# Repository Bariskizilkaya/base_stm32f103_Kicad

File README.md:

# base_stm32f103_Kicad
Kicad based stm32f103 base desing

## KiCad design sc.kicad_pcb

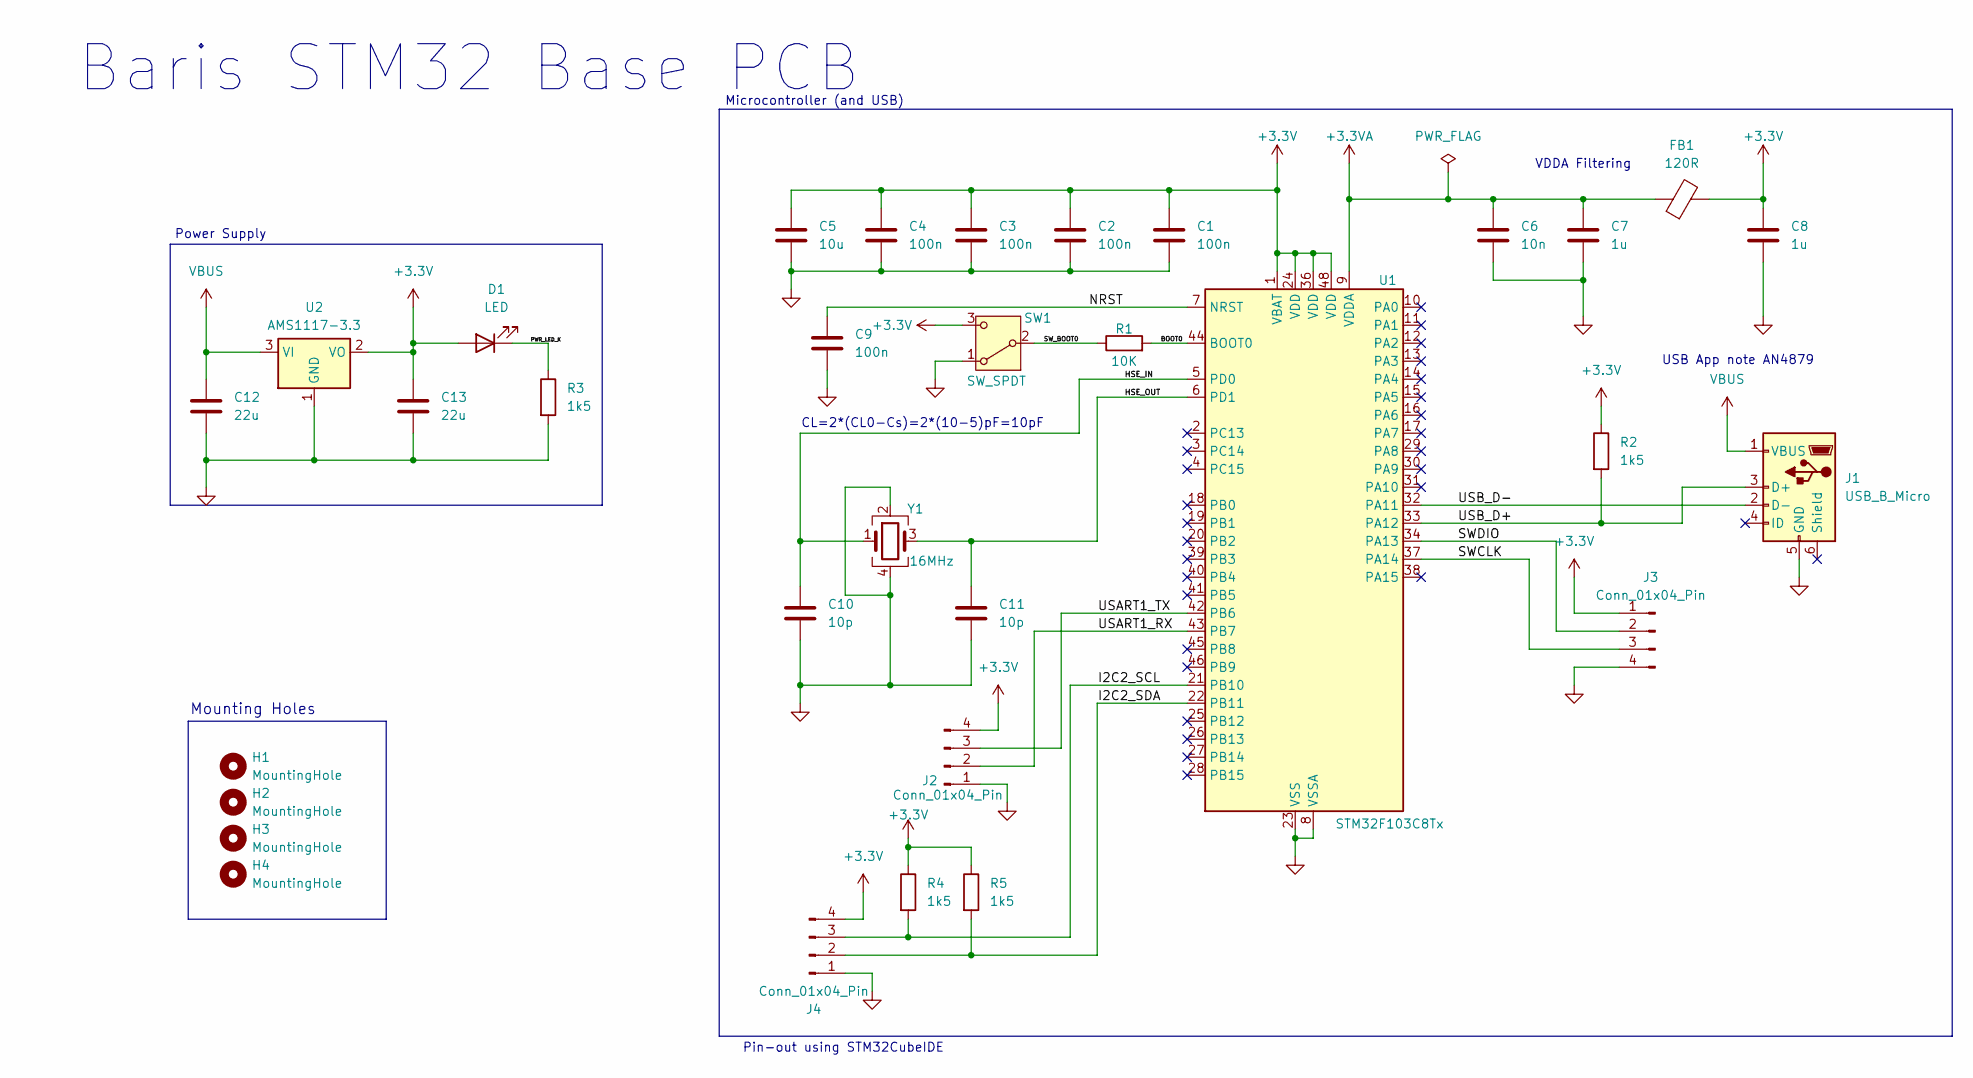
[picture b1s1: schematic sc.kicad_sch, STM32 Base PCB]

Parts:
C1, C2, C3, C4, C9: 100n; C_0402_1005Metric
C5: 10u; C_0603_1608Metric
C6: 10n; C_0402_1005Metric
C7, C8: 1u; C_0402_1005Metric
C10, C11: 10p; C_0402_1005Metric
C12, C13: 22u; C_0805_2012Metric
D1: LED; LED_0603_1608Metric
FB1: 120R; L_0603_1608Metric
H1, H2, H3, H4: MountingHole; MountingHole_2.2mm_M2
J1: USB_B_Micro; USB_Micro-B_Wuerth_629105150521
J2, J3, J4: Conn_01x04_Pin; PinHeader_1x04_P2.54mm_Vertical
R1: 10K; R_0402_1005Metric
R2, R3, R4, R5: 1k5; R_0402_1005Metric
SW1: SW_SPDT; SW_SPDT_PCM12
U1: STM32F103C8Tx; LQFP-48_7x7mm_P0.5mm
U2: AMS1117-3.3; SOT-223-3_TabPin2
Y1: 16MHz; Crystal_SMD_3225-4Pin_3.2x2.5mm

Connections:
+3.3V: C1.1, C2.1, C3.1, C4.1, C5.1, C8.1, C13.1, D1.2 (A), FB1.2, J2.4, J3.1, J4.4, R2.1, R4.1, R5.1, SW1.3 (C), U1.1 (VBAT), U1.24 (VDD), U1.36 (VDD), U1.48 (VDD), U2.2 (VO)
+3.3VA: C6.1, C7.1, FB1.1, U1.9 (VDDA)
/BOOT0: R1.2, U1.44 (BOOT0)
/HSE_IN: C10.1, U1.5 (PD0), Y1.1
/HSE_OUT: C11.1, U1.6 (PD1), Y1.3
/I2C2_SCL: J4.3, R4.2, U1.21 (PB10)
/I2C2_SDA: J4.2, R5.2, U1.22 (PB11)
/NRST: C9.1, U1.7 (NRST)
/PWR_LED_K: D1.1 (K), R3.1
/SWCLK: J3.3, U1.37 (PA14)
/SWDIO: J3.2, U1.34 (PA13)
/SW_BOOT0: R1.1, SW1.2 (B)
/USART1_RX: J2.2, U1.43 (PB7)
/USART1_TX: J2.3, U1.42 (PB6)
/USB_D+: J1.3 (D+), R2.2, U1.33 (PA12)
/USB_D-: J1.2 (D-), U1.32 (PA11)
GND: C1.2, C2.2, C3.2, C4.2, C5.2, C6.2, C7.2, C8.2, C9.2, C10.2, C11.2, C12.2, C13.2, J1.5 (GND), J2.1, J3.4, J4.1, R3.2, SW1.1 (A), U1.8 (VSSA), U1.23 (VSS), U1.35 (VSS), U1.47 (VSS), U2.1 (GND), Y1.2, Y1.4
VBUS: C12.1, J1.1 (VBUS), U2.3 (VI)

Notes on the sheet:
Mounting Holes
Power Supply
Pin-out using STM32CubeIDE
VDDA Filtering
CL=2*(CL0-Cs)=2*(10-5)pF=10pF
Baris STM32 Base PCB
Microcontroller (and USB)
USB App note AN4879

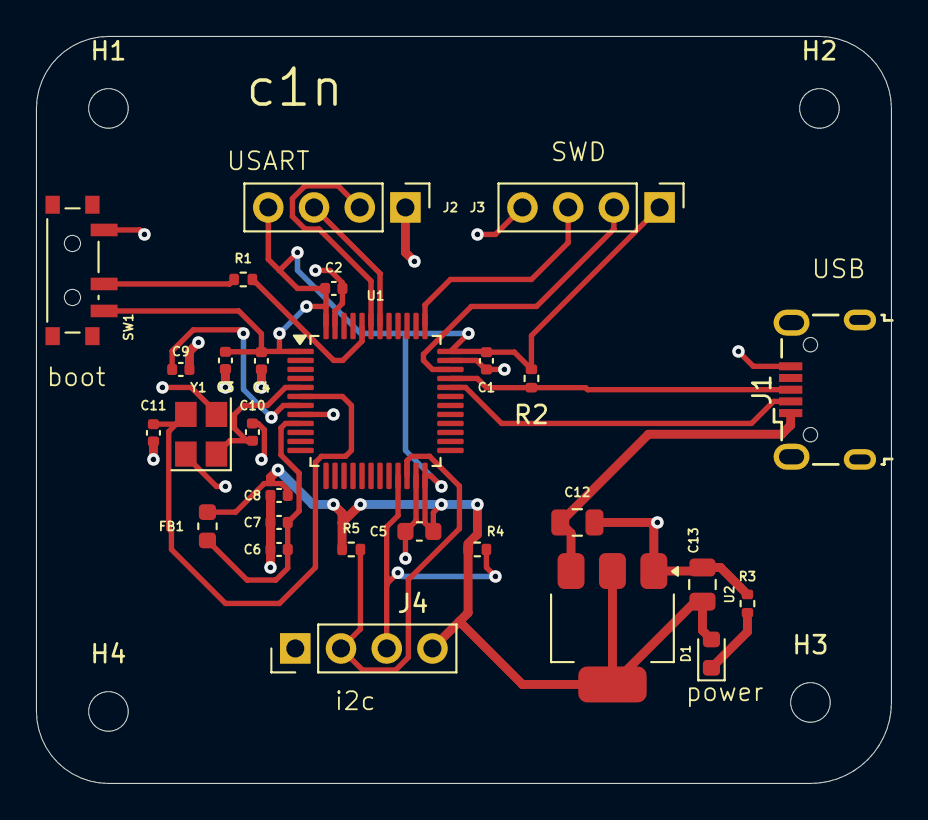
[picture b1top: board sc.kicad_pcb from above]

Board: 2 copper layers, 47.5 x 41.5 mm, 32 parts (0 on the bottom side), 18 nets.

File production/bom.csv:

Designator,Footprint,Quantity,Value,LCSC Part #
"C1, C2, C3, C4, C9",0402,5,100n,
"C10, C11",0402,2,10p,
"C12, C13",0805,2,22u,
C5,0603,1,10u,
C6,0402,1,10n,
"C7, C8",0402,2,1u,
D1,0603,1,LED,
FB1,0603,1,120R,
J1,USB_Micro-B_Wuerth_629105150521,1,USB_B_Micro,
"J2, J3, J4",PinHeader_1x04_P2.54mm_Vertical,3,Conn_01x04_Pin,
R1,0402,1,10K,
"R2, R3, R4, R5",0402,4,1k5,
SW1,SW_SPDT_PCM12,1,SW_SPDT,
U1,LQFP-48_7x7mm_P0.5mm,1,STM32F103C8Tx,
U2,SOT-223-3_TabPin2,1,AMS1117-3.3,
Y1,Crystal_SMD_3225-4Pin_3.2x2.5mm,1,16MHz,

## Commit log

2024-11-02 init
